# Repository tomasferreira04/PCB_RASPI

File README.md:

# PCB_RASPI
MPPT solar charger controller with a DC/DC boost controller for Raspberry Pi and GSM with Peripheral outputs for GPIO
Design on Autodesk EAGLE.

This PCB is a power management controller for Solar pannels and Li-po batteries.
As 2 40pin GPIO headers for raspberry pi and gsm connection
As 5 I/O for fans, leds, buttons and sensors.
1 USB-A output for 5V/1A to provide power for Raspberry Pi.

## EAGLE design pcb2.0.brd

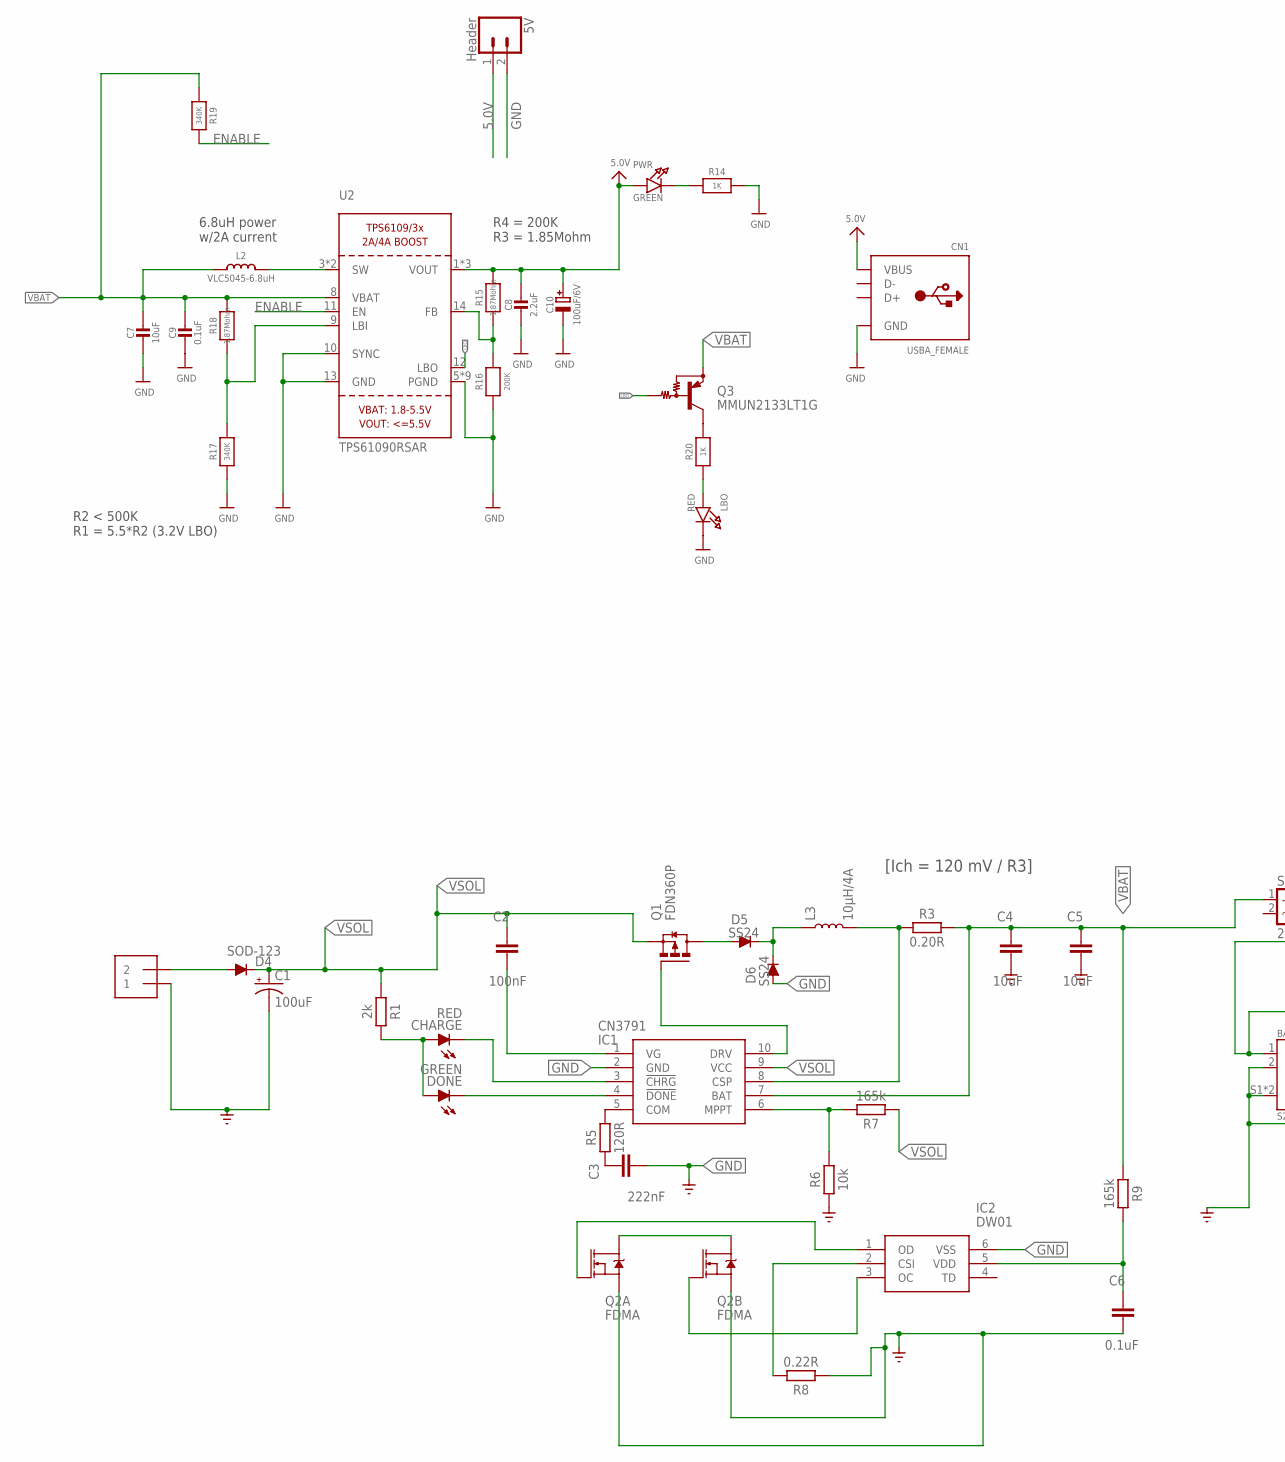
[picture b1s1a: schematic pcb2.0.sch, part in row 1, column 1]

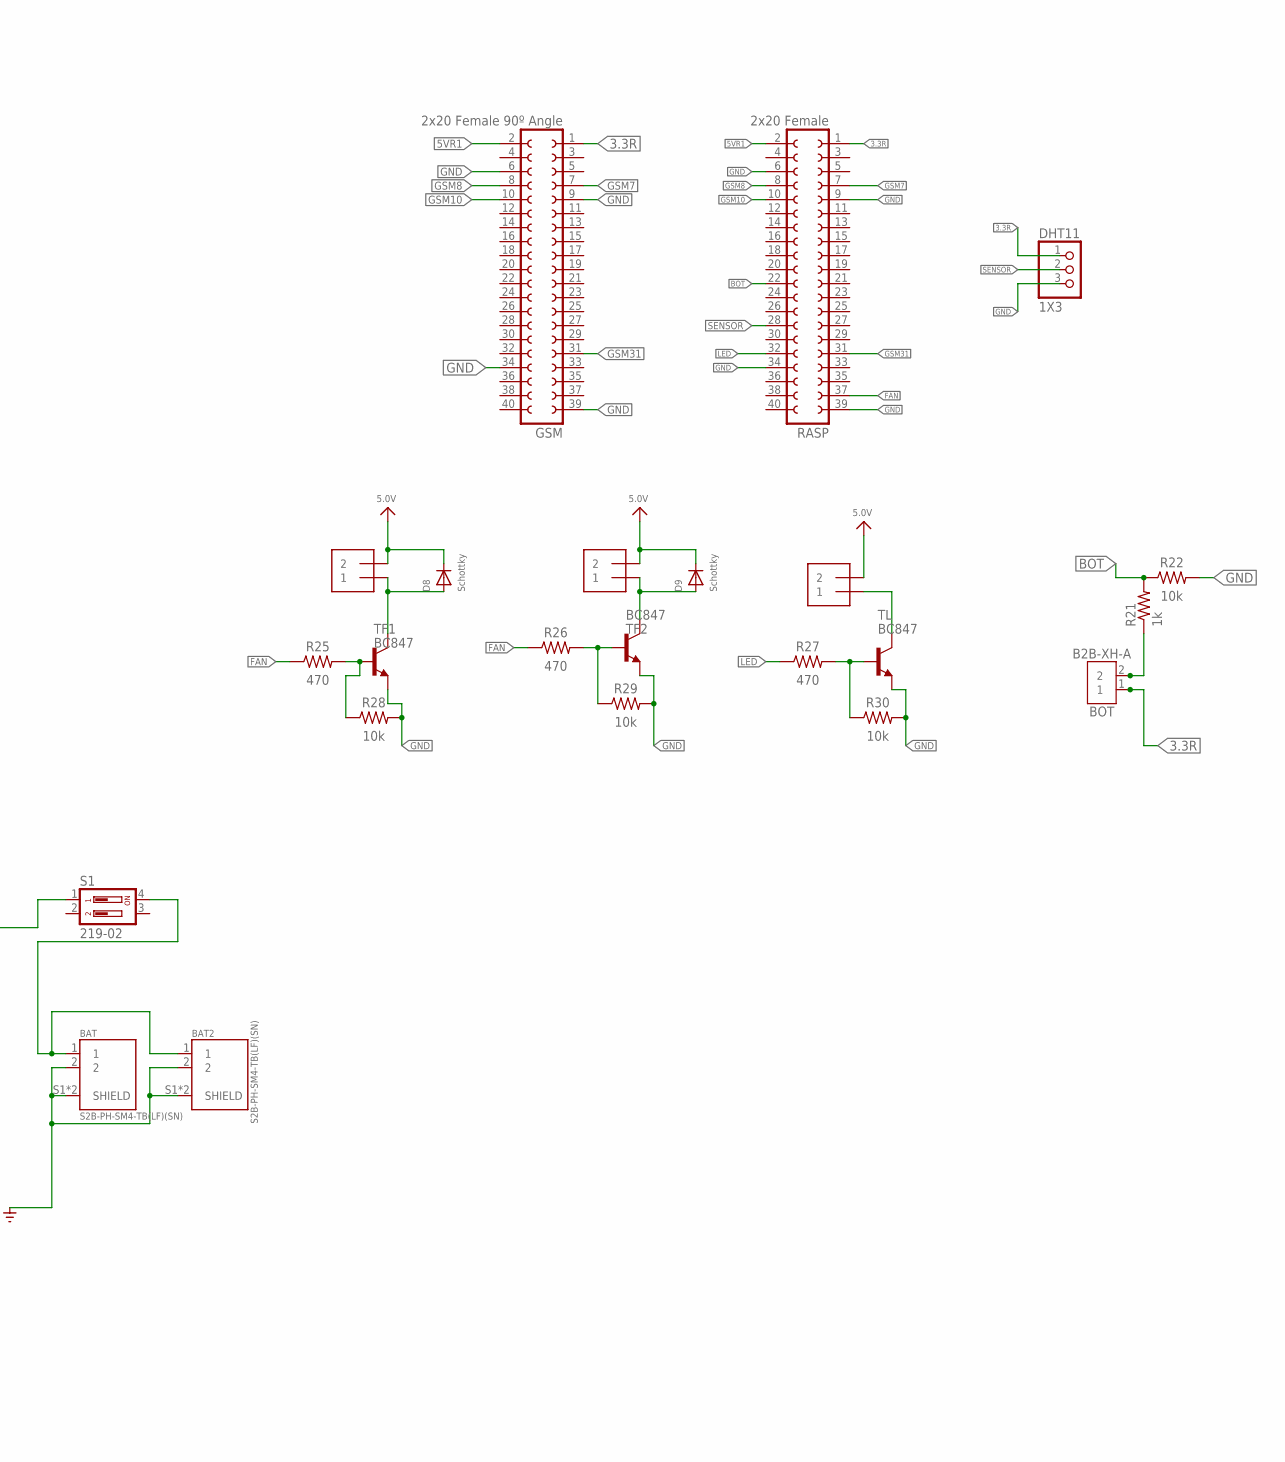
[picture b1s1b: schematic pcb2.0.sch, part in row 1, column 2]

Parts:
5V: Header; 1X02
BAT, BAT2: S2B-PH-SM4-TB(LF)(SN)
BOT: B2B-XH-A
C1: 100uF; 153CLV-0505
C2: 100nF; CAP_0603
C3: 222nF; CAP_0603
C4, C5: 10uF; CAP_0603
C6: 0.1uF; CAP_0603
C7: 10uF; 0805-NO
C8: 2.2uF; 0805-NO
C9: 0.1uF; 0805-NO
C10: 100uF/6V; EIA3528-21/B-R
CHARGE: RED; LED_CHIP-LED0603MP
CN1: USBA_FEMALE; USB_HOST-PTH
D4: SOD-123; DIODE_SOD123
D5, D6: SS24; DIODE_SOD123
D8, D9: Schottky; SOD-123
DHT11: 1X3; 1X03
DONE: GREEN; LED_CHIP-LED0603MP
FAN1, FAN2: 1X2-3.5MM
GSM: 2x20 Female 90º Angle; FE20-2W
IC1: CN3791; SOP100P600X175-10N
IC2: DW01; SOT95P280X135-6N
L2: VLC5045-6.8uH; INDUCTOR_5X5MM_TDK_VLC5045
L3: 10µH/4A; CR54
LBO: RED; CHIPLED_0805_NOOUTLINE
LED: 1X2-3.5MM
PWR: GREEN; CHIPLED_0805_NOOUTLINE
Q1: FDN360P; SUPER-SOT3
Q2: FDMA; MICROFET_2X2
Q3: MMUN2133LT1G; SC59-BEC
R1: 2k; RESC1608X60
R3: 0.20R; RESC1608X60
R5: 120R; RESC1608X60
R6: 10k; RESC1608X60
R7, R9: 165k; RESC1608X60
R8: 0.22R; RESC1608X60
R14, R20: 1K; 0805-NO
R15, R18: 1.87Mohm; 0805-NO
R16: 200K; 0805-NO
R17, R19: 340K; 0805-NO
R21: 1k; R0805
R22, R28, R29, R30: 10k; RESC2012X65
R25, R26, R27: 470; RESC2012X65
RASP: 2x20 Female; FE20-2
S1: 219-02; CTS-219-02
TF1, TF2: BC847; SOT23
TL: BC847; SOT23
U2: TPS61090RSAR; PVQFN-16
VIN: 1X2-3.5MM

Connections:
3.3R: BOT.1, DHT11.1, GSM.1, RASP.1
5.0V: 5V.1, C8.1, C10.+, CN1.VBUS, D8.C, D9.C, FAN1.2, FAN2.2, LED.2, PWR.A, R15.2, U2.1 (VOUT), U2.15 (VOUT), U2.16 (VOUT)
5VR1: GSM.2, RASP.2
BOT: R21.2, R22.1, RASP.22
ENABLE: R19.2, U2.11 (EN)
FAN: R25.1, R26.1, RASP.37
GND: 5V.2, BAT.2, BAT.S1 (SHIELD), BAT.S2 (SHIELD), BAT2.2, BAT2.S1 (SHIELD), BAT2.S2 (SHIELD), C1.-, C3.2, C4.2, C5.2, C6.2, C7.2, C8.2, C9.2, C10.-, CN1.GND, D6.A, DHT11.3, GSM.6, GSM.9, GSM.34, GSM.39, IC1.2 (GND), IC2.6 (VSS), LBO.C, Q2.S1 (S), Q2.S2 (S), R6.1, R8.1, R14.2, R16.1, R17.1, R22.2, R28.2, R29.2, R30.2, RASP.6, RASP.9, RASP.34, RASP.39, TF1.2 (E), TF2.2 (E), TL.2 (E), U2.5 (PGND), U2.6 (PGND), U2.7 (PGND), U2.10 (SYNC), U2.13 (GND), U2.P$18 (PGND), U2.P$19 (PGND), U2.P$20 (PGND), U2.P$21 (PGND), U2.P$22 (PGND), U2.THERMAL (PGND), VIN.1
GSM7: GSM.7, RASP.7
GSM8: GSM.8, RASP.8
GSM10: GSM.10, RASP.10
GSM31: GSM.31, RASP.31
LBO: Q3.B, U2.12 (LBO)
LED: R27.1, RASP.32
unnamed: L2.P$2 (2), U2.3 (SW), U2.4 (SW)
unnamed: C2.2, IC1.1 (VG)
unnamed: CHARGE.C, IC1.3 (!CHRG)
unnamed: IC1.8 (CSP), L3.P$2 (2), R3.1
unnamed: CHARGE.A, DONE.A, R1.2
unnamed: DONE.C, IC1.4 (!DONE)
unnamed: IC1.5 (COM), R5.2
unnamed: C3.1, R5.1
unnamed: IC1.10 (DRV), Q1.1 (G)
unnamed: R17.2, R18.1, U2.9 (LBI)
unnamed: D5.A, Q1.3 (D)
unnamed: D5.C, D6.C, L3.P$1 (1)
unnamed: IC1.6 (MPPT), R6.2, R7.2
unnamed: Q2.D1 (D), Q2.D1_2 (D), Q2.D2 (D), Q2.D2_2 (D)
unnamed: BAT.1, BAT2.1, S1.4
unnamed: IC2.1 (OD), Q2.G1 (G)
unnamed: IC2.3 (OC), Q2.G2 (G)
unnamed: C6.1, IC2.5 (VDD), R9.2
unnamed: IC2.2 (CSI), R8.2
unnamed: BOT.2, R21.1
unnamed: PWR.C, R14.1
unnamed: LBO.A, R20.1
unnamed: Q3.C, R20.2
unnamed: R15.1, R16.2, U2.14 (FB)
unnamed: R25.2, R28.1, TF1.1 (B)
unnamed: R26.2, R29.1, TF2.1 (B)
unnamed: R27.2, R30.1, TL.1 (B)
unnamed: D8.A, FAN1.1, TF1.3 (C)
unnamed: D9.A, FAN2.1, TF2.3 (C)
unnamed: LED.1, TL.3 (C)
SENSOR: DHT11.2, RASP.28
VBAT: C4.1, C5.1, C7.1, C9.1, IC1.7 (BAT), L2.P$1 (1), Q3.E, R3.2, R9.1, R18.2, R19.1, S1.1, U2.8 (VBAT)
VSOL: C1.+, C2.1, D4.C, IC1.9 (VCC), Q1.2 (S), R1.1, R7.1
VSOLAR: D4.A, VIN.2

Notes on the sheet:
6.8uH power w/2A current
R2 < 500K R1 = 5.5*R2 (3.2V LBO)
R4 = 200K R3 = 1.85Mohm
[Ich = 120 mV / R3]

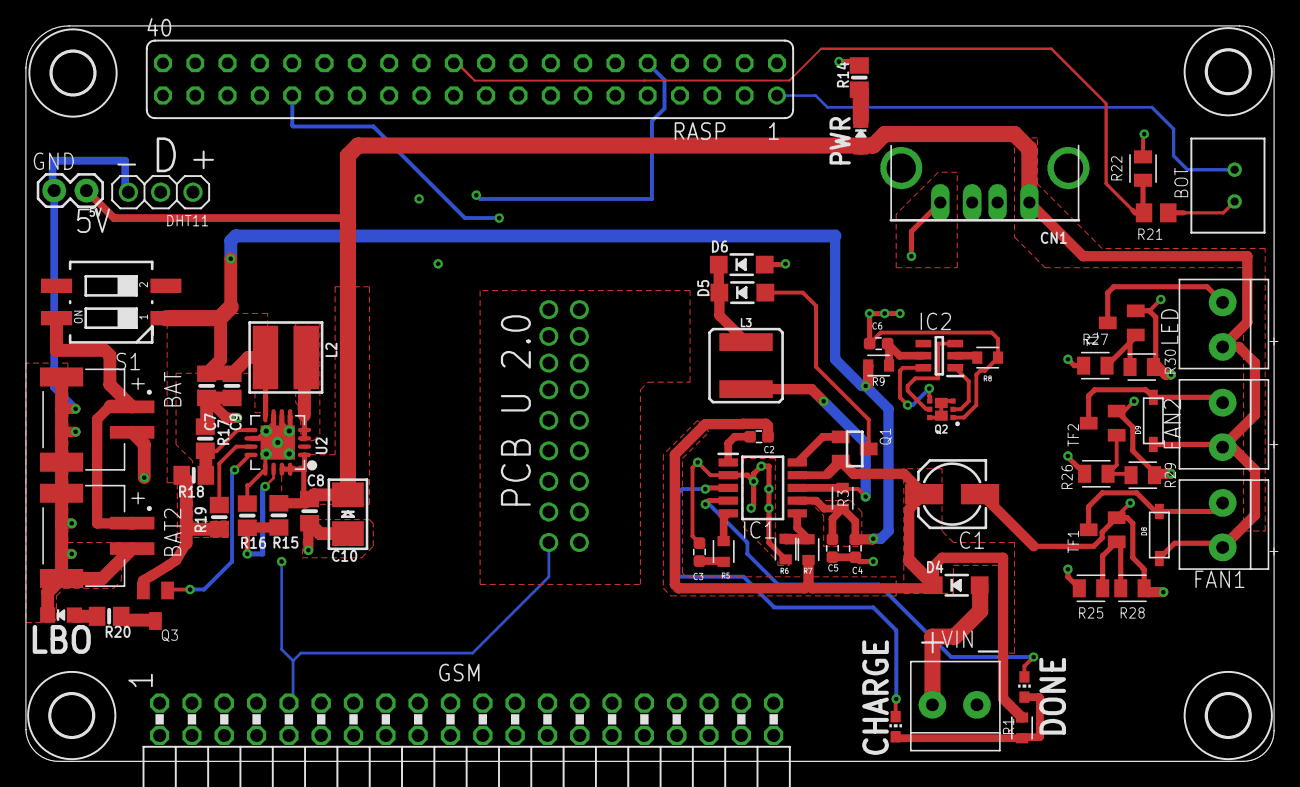
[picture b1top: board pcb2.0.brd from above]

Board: 4 copper layers, 98.1 x 57.8 mm, 69 parts (0 on the bottom side), 47 nets.

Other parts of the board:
U$5, U$9, U$10, U$11: 3,3

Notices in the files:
parts and their libraries:
SparkFun-Connectors: Licensing: Creative Commons ShareAlike 4.0 International - https://creativecommons.org/licenses/by-sa/4.0
microbuilder: This work is placed in the public domain, and may be freely used for commercial and non-commercial work with the following conditions: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
